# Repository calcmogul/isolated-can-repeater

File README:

Hardware
--------
Microcontroller (MSP430G2553) x1
* http://www.digikey.com/product-detail/en/texas-instruments/MSP430G2553IN20/296-28429-5-ND/2638885

Socket (2x7 0.3" row spacing) x1
* http://www.digikey.com/product-detail/en/mill-max-manufacturing-corp/110-44-314-41-001000/ED90049-ND/947057

Inverter (CD4069UBE) x1
* http://www.digikey.com/product-detail/en/texas-instruments/CD4069UBE/296-3518-5-ND/376616

NOR (CD4001UBE) x1
* http://www.digikey.com/product-detail/en/texas-instruments/CD4001UBE/296-14077-5-ND/525852

CAN Transceiver (ISO1050SUBR) x2
* http://www.digikey.com/product-detail/en/texas-instruments/ISO1050DUBR/296-24818-2-ND/2094633

Voltage Regulator 3.3V (LD117AV33) x1
* https://www.sparkfun.com/products/526

0.1μF Capacitor x1
* http://www.digikey.com/product-detail/en/vishay-bc-components/K104Z15Y5VF5TL2/BC1160CT-ND/286782

10μF Capacitor x1
* http://www.digikey.com/product-detail/en/tdk-corporation/FK24X5R1C106K/445-8497-ND/2815427

MSP430 Software Dependencies
----------------------------
* msp430-elf-gcc
* mspdebug

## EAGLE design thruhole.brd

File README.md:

# Galvanically Isolated CAN Repeater

This PCB is designed to function as a CAN repeater that galvanically isolates the two sides of the bus. It uses the repeater logic in figure 3 of AND8358/D (the application note for the AMIS-42700's feedback suppression).

## Hardware

* [Microcontroller](http://www.digikey.com/product-detail/en/texas-instruments/MSP430G2553IN20/296-28429-5-ND/2638885) (MSP430G2553) x1
* [Socket](http://www.digikey.com/product-detail/en/assmann-wsw-components/AR-20-HZL-TT/AE10015-ND/821769) (2x10 0.3" row spacing) x1
* [NOT Gates](http://www.digikey.com/product-detail/en/texas-instruments/CD4069UBE/296-3518-5-ND/376616) (CD4069UBE) x1
* [NAND Gates](http://www.digikey.com/product-detail/en/texas-instruments/CD4011BE/296-2031-5-ND/67241) (CD4011UBE) x1
* [CAN Transceiver](http://www.digikey.com/product-detail/en/texas-instruments/ISO1050DUBR/296-24818-2-ND/2094633) (ISO1050SUBR) x2
* [Voltage Regulator 3.3V](https://www.digikey.com/product-detail/en/stmicroelectronics/LD1117V33/497-1491-5-ND/586012) (LD1117V33) x1
* [0.1μF Capacitor](http://www.digikey.com/product-detail/en/vishay-bc-components/K104Z15Y5VF5TL2/BC1160CT-ND/286782) x1
* [10μF Capacitor](http://www.digikey.com/product-detail/en/tdk-corporation/FK24X5R1C106K/445-8497-ND/2815427) x1

### Thruhole

* 1x4 pin header x3

### SMT

* 2x6 pin header x1

## MSP430 Software

See [MSP430 README](msp430/README.md).

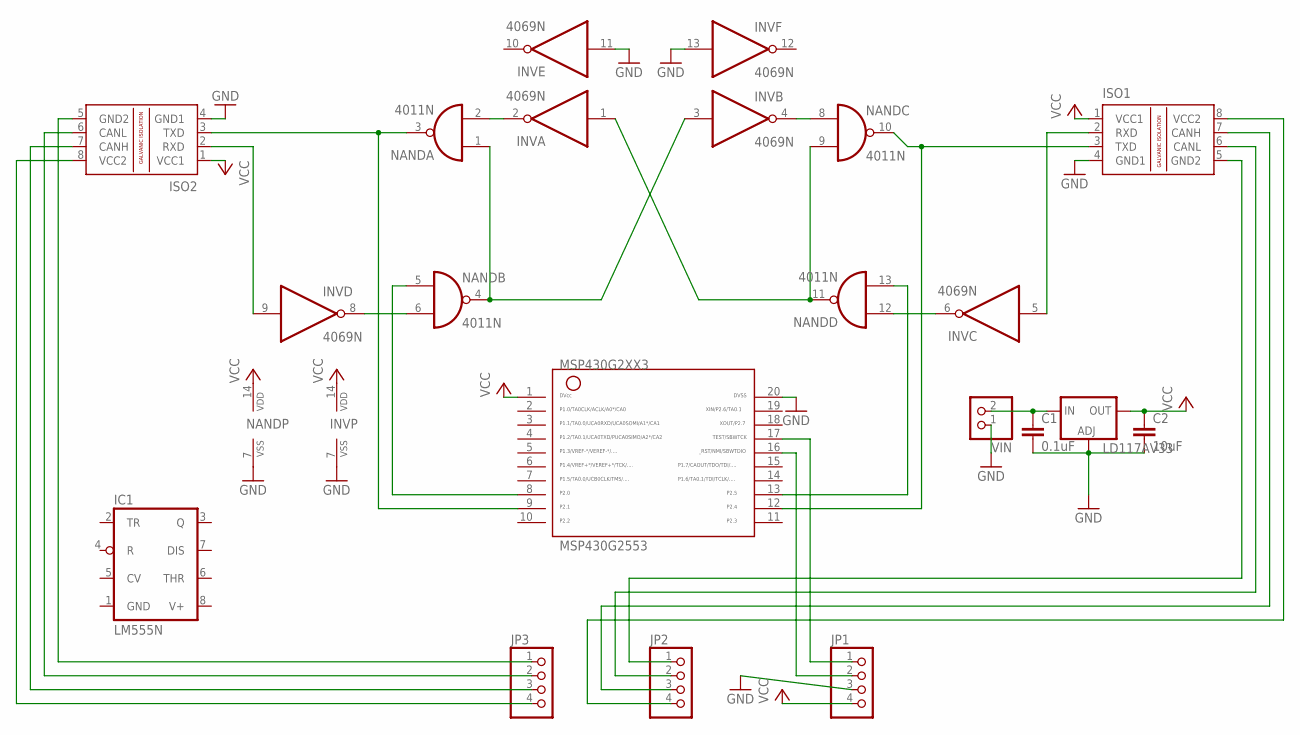
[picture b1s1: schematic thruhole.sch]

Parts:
C1: 0.1uF; C025-024X044
C2: 10uF; C025-024X044
IC1: LM555N; DIL08
INV: 4069N; DIL14
ISO1, ISO2: ISO1050DUB; DUB-R-PDSO-G8
JP1, JP2, JP3: PINHD-1X4; 1X04
LD117AV33: LD117AV33; TO220L1
MSP430G2553: G2XX3---N20; N20
NAND: 4011N; DIL14
VIN: PINHD-1X2; 1X02

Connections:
GND: C1.2, C2.2, IC1.1 (GND), INV.7 (VSS), INV.11 (I), INV.13 (I), ISO1.4 (GND1), ISO2.4 (GND1), JP1.3, LD117AV33.1 (ADJ), MSP430G2553.20, NAND.7 (VSS), VIN.1
unnamed: JP1.2, MSP430G2553.16
unnamed: JP1.1, MSP430G2553.17
unnamed: INV.8 (O), NAND.6 (I1)
unnamed: INV.2 (O), NAND.2 (I1)
unnamed: INV.4 (O), NAND.8 (I0)
unnamed: INV.6 (O), NAND.12 (I0)
unnamed: INV.1 (I), NAND.9 (I1), NAND.11 (O)
unnamed: INV.3 (I), NAND.1 (I0), NAND.4 (O)
unnamed: ISO2.8 (VCC2), JP3.4
unnamed: ISO2.7 (CANH), JP3.3
unnamed: ISO2.6 (CANL), JP3.2
unnamed: ISO2.5 (GND2), JP3.1
unnamed: ISO1.8 (VCC2), JP2.4
unnamed: ISO1.7 (CANH), JP2.3
unnamed: ISO1.6 (CANL), JP2.2
unnamed: ISO1.5 (GND2), JP2.1
unnamed: INV.5 (I), ISO1.2 (RXD)
unnamed: INV.9 (I), ISO2.2 (RXD)
unnamed: MSP430G2553.8, NAND.5 (I0)
unnamed: MSP430G2553.13, NAND.13 (I1)
unnamed: C1.1, LD117AV33.3 (IN), VIN.2
unnamed: ISO2.3 (TXD), MSP430G2553.9, NAND.3 (O)
unnamed: ISO1.3 (TXD), MSP430G2553.12, NAND.10 (O)
V+: IC1.8 (V+)
VCC: C2.1, INV.14 (VDD), ISO1.1 (VCC1), ISO2.1 (VCC1), JP1.4, LD117AV33.2 (OUT), MSP430G2553.1, NAND.14 (VDD)

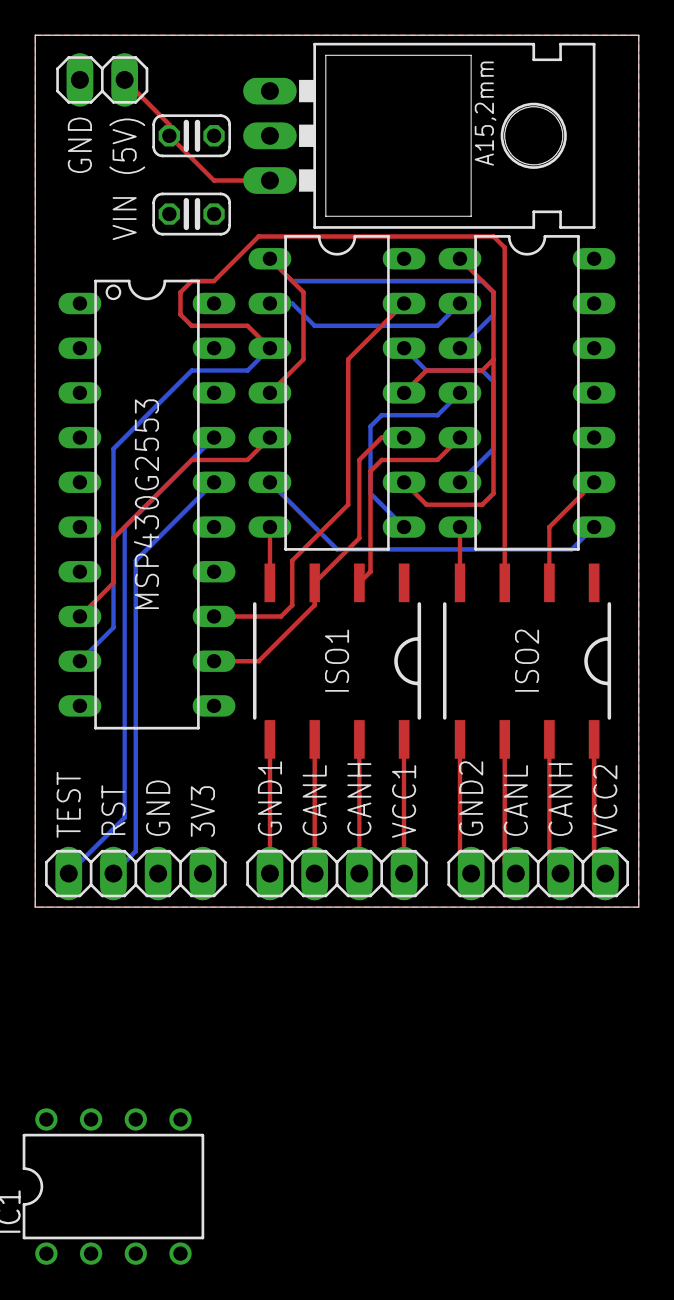
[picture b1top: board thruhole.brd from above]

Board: 2 copper layers, 34.3 x 49.5 mm, 13 parts (0 on the bottom side), 25 nets.

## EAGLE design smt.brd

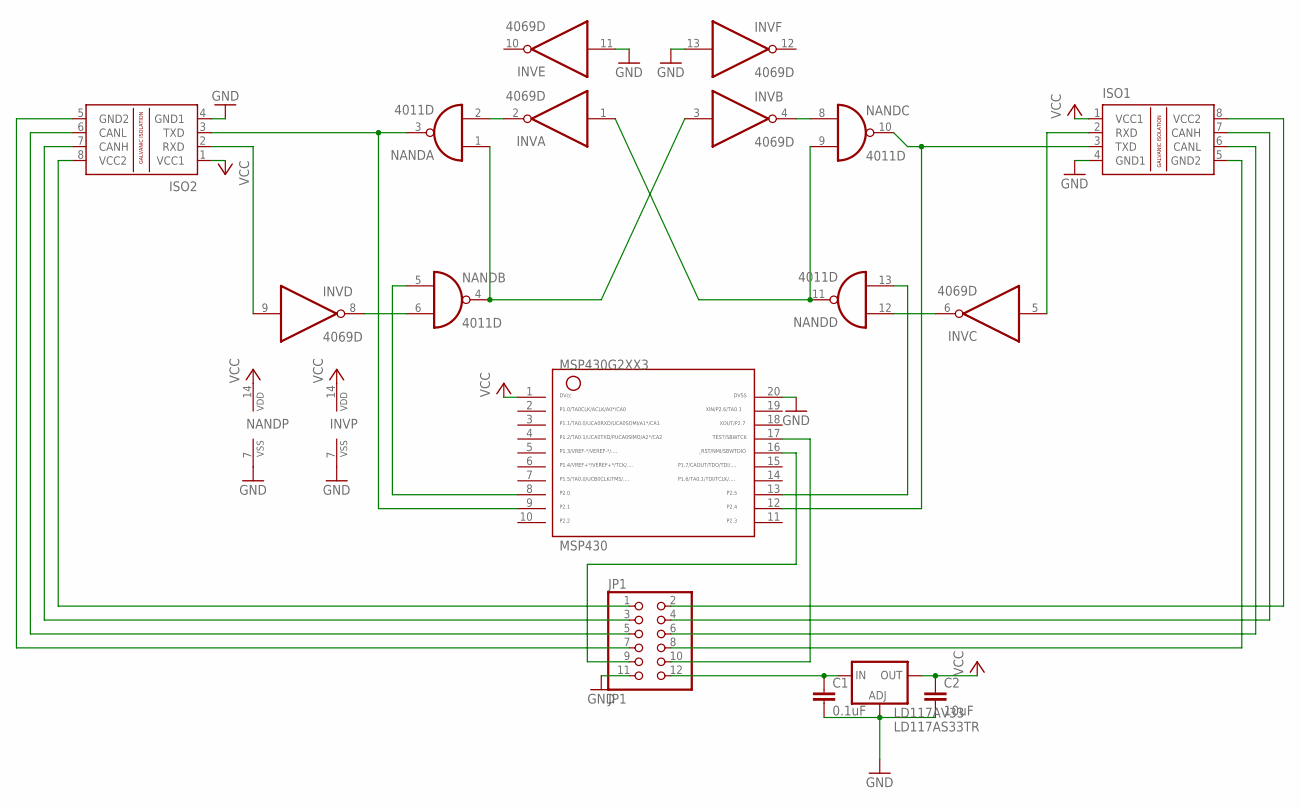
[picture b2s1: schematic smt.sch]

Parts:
C1: 0.1uF; C0402
C2: 10uF; C0402
INV: 4069D; SO14
ISO1, ISO2: ISO1050DUB; DUB-R-PDSO-G8
JP1: JP1; 2X06
LD117AV33: LD117AS33TR; SOT223
MSP430: G2XX3---PW20; PW20
NAND: 4011D; SO14

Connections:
GND: C1.2, C2.2, INV.7 (VSS), INV.11 (I), INV.13 (I), ISO1.4 (GND1), ISO2.4 (GND1), JP1.11, LD117AV33.1 (ADJ), MSP430.20, NAND.7 (VSS)
unnamed: JP1.9, MSP430.16
unnamed: JP1.10, MSP430.17
unnamed: INV.8 (O), NAND.6 (I1)
unnamed: INV.2 (O), NAND.2 (I1)
unnamed: INV.4 (O), NAND.8 (I0)
unnamed: INV.6 (O), NAND.12 (I0)
unnamed: INV.1 (I), NAND.9 (I1), NAND.11 (O)
unnamed: INV.3 (I), NAND.1 (I0), NAND.4 (O)
unnamed: ISO2.8 (VCC2), JP1.1
unnamed: ISO2.7 (CANH), JP1.3
unnamed: ISO2.6 (CANL), JP1.5
unnamed: ISO2.5 (GND2), JP1.7
unnamed: ISO1.8 (VCC2), JP1.2
unnamed: ISO1.7 (CANH), JP1.4
unnamed: ISO1.6 (CANL), JP1.6
unnamed: ISO1.5 (GND2), JP1.8
unnamed: INV.5 (I), ISO1.2 (RXD)
unnamed: INV.9 (I), ISO2.2 (RXD)
unnamed: MSP430.8, NAND.5 (I0)
unnamed: MSP430.13, NAND.13 (I1)
unnamed: C1.1, JP1.12, LD117AV33.3 (IN)
unnamed: ISO2.3 (TXD), MSP430.9, NAND.3 (O)
unnamed: ISO1.3 (TXD), MSP430.12, NAND.10 (O)
VCC: C2.1, INV.14 (VDD), ISO1.1 (VCC1), ISO2.1 (VCC1), LD117AV33.4 (OUT), MSP430.1, NAND.14 (VDD)

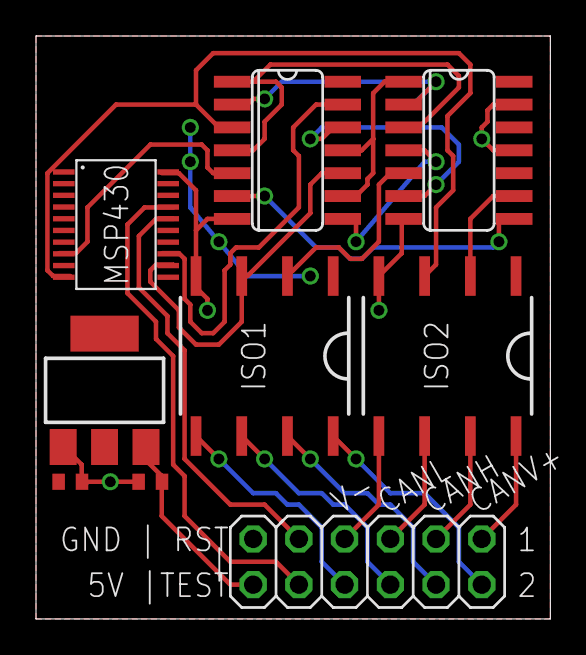
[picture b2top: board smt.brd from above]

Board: 2 copper layers, 28.6 x 32.4 mm, 9 parts (0 on the bottom side), 25 nets.

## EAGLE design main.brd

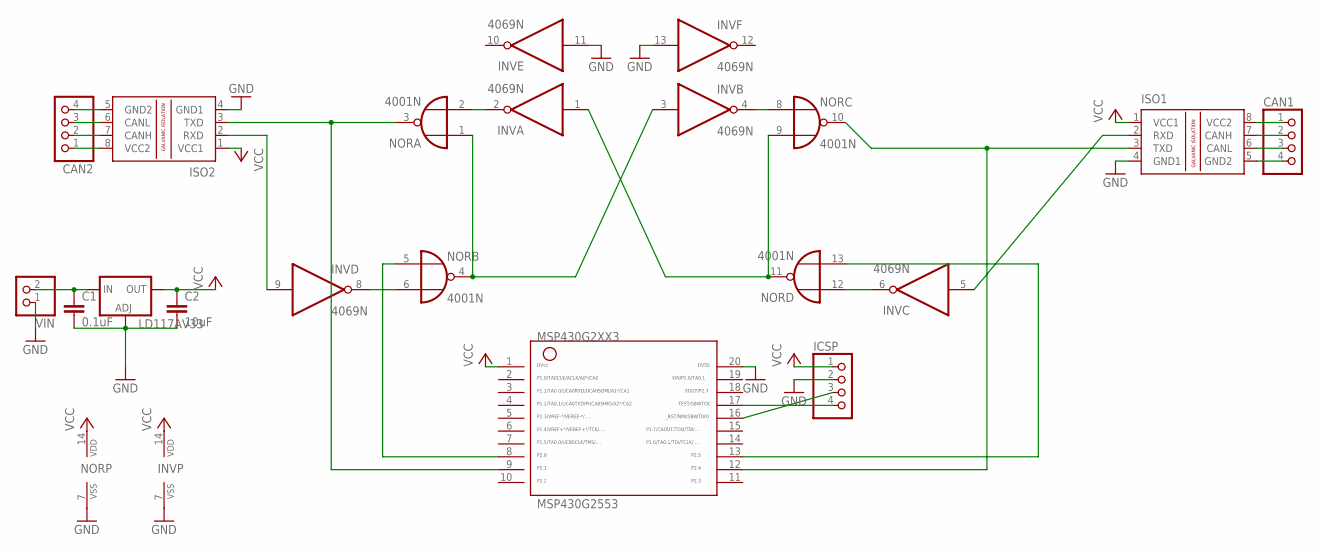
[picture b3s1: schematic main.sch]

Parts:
C1: 0.1uF; C025-024X044
C2: 10uF; C025-024X044
CAN1, CAN2: PINHD-1X4; 1X04
ICSP: PINHD-1X4; 1X04
INV: 4069N; DIL14
ISO1, ISO2: ISO1050DUB; DUB-R-PDSO-G8
LD117AV33: LD117AV33; TO220L1
MSP430G2553: G2XX3---N20; N20
NOR: 4001N; DIL14
VIN: PINHD-1X2; 1X02

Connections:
GND: C1.2, C2.2, ICSP.2, INV.7 (VSS), INV.11 (I), INV.13 (I), ISO1.4 (GND1), ISO2.4 (GND1), LD117AV33.1 (ADJ), MSP430G2553.20, NOR.7 (VSS), VIN.1
unnamed: ICSP.3, MSP430G2553.16
unnamed: ICSP.4, MSP430G2553.17
unnamed: INV.8 (O), NOR.6 (I1)
unnamed: INV.2 (O), NOR.2 (I1)
unnamed: INV.4 (O), NOR.8 (I0)
unnamed: INV.6 (O), NOR.12 (I0)
unnamed: INV.1 (I), NOR.9 (I1), NOR.11 (O)
unnamed: INV.3 (I), NOR.1 (I0), NOR.4 (O)
unnamed: CAN2.1, ISO2.8 (VCC2)
unnamed: CAN2.2, ISO2.7 (CANH)
unnamed: CAN2.3, ISO2.6 (CANL)
unnamed: CAN2.4, ISO2.5 (GND2)
unnamed: CAN1.1, ISO1.8 (VCC2)
unnamed: CAN1.2, ISO1.7 (CANH)
unnamed: CAN1.3, ISO1.6 (CANL)
unnamed: CAN1.4, ISO1.5 (GND2)
unnamed: INV.5 (I), ISO1.2 (RXD)
unnamed: INV.9 (I), ISO2.2 (RXD)
unnamed: MSP430G2553.8, NOR.5 (I0)
unnamed: MSP430G2553.13, NOR.13 (I1)
unnamed: C1.1, LD117AV33.3 (IN), VIN.2
unnamed: ISO2.3 (TXD), MSP430G2553.9, NOR.3 (O)
unnamed: ISO1.3 (TXD), MSP430G2553.12, NOR.10 (O)
VCC: C2.1, ICSP.1, INV.14 (VDD), ISO1.1 (VCC1), ISO2.1 (VCC1), LD117AV33.2 (OUT), MSP430G2553.1, NOR.14 (VDD)

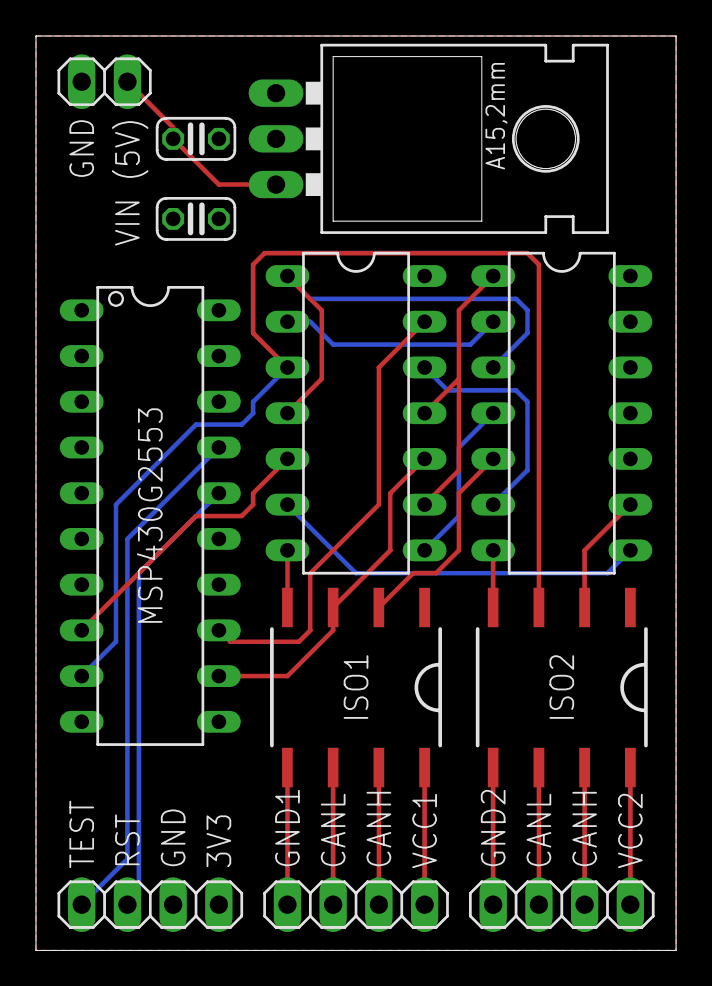
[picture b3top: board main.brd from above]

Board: 2 copper layers, 35.6 x 50.8 mm, 12 parts (0 on the bottom side), 25 nets.

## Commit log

2016-12-14 Pin pitch of TI's MSP430 N20 package now aligns with grid
2016-12-14 Reduced board height a bit
2016-12-15 Replaced MSP430 with correct IC (MSP430G2553), improved board annotations, and added parts list to README
2016-12-17 Moved some traces to the top layer
2016-12-17 Chose different socket
2016-12-17 PCB tweaks in pursuit of a planar design (not working)
2016-12-17 Moved some traces to the bottom layer to fix plane isolation and shorten the trace lengths
2016-12-17 Shrunk the board height a bit
2016-12-17 Rotated gates 90 CCW to achieve smaller board with much shorter traces
2016-12-18 Added pin annotations
2016-12-18 Chose different 10uF capacitor and updated links to capacitors
2016-12-18 msp430: finished initial implementation
2016-12-18 Ran wpiformat
2016-12-18 Replaced incorrect component and converted README to Markdown
    Replaced NOR gates with NAND gates to match AMIS schematic and updated parts list to reflect the change.
2016-12-18 Added pin headers to parts list and replaced listed socket
2016-12-18 msp430: added more comments and fixed a few bit twiddling typos
2016-12-20 Created SMT version of PCB
2016-12-20 Removed eagle.epf file from version control
2016-12-22 Moved components on thruhole board closer together and swapped pin headers for 1x12 pin header
2016-12-22 Adjusted SMT board pin labels
2016-12-23 msp430: software was tested with a logic analyzer and debugged
    The GPIO interrupts were replaced with a software loop to avoid simultaneous GPIO rising and falling edges.
2016-12-23 Separated thruhole 1x12 pin header into 3 1x4 pin headers for rules compliance
2016-12-24 Removed debugging modifications
2016-12-24 Reorganized schematics
2017-01-16 Removed errant trace from SMT board
2017-05-26 Replaced SparkFun voltage regulator link with one from Digi-Key
2017-05-26 WIP: Added 555 timer to thruhole board
